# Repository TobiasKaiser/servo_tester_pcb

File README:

TO-263 footprint from https://github.com/cpavlina/kicad-pcblib

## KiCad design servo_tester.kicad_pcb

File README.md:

servo_tester
============
*An electronics project for me to learn how to design PCBs in KiCad and assemble it with SMD components.*

Purpose
-------

* Generate a PWM signal of approximately 20 ms period with variable duty cycle.
* The duty cycle can be controlled by a potentiometer.
* For user feedback, the currently set value should be displayed on a 4 digit seven-segment display.
* Through an additional push button, the user should be able to cycle through a number of settings to control parameters of the PWM output.
* This PWM output can be used to control the position of a servo motor.
* To have more, interesting stuff on the board, I put a little buck converter (instead of a linear voltage regulator like the 7805) on the board.

Hardware
--------

**Corrected** circuit here:
...

**Note: Some of the hardware problems which are corrected in this circuit file are not yet corrected in the board file.**

Hardware Problems
-----------------

As I expected, not everything worked out with the first PCBs and components that I have ordered. 

* Before the manufactured PCBs arrived, I already noticed that R5, R6, R7, R8 are incorrectly placed at the common electrode of the multiplexed seven-segment LED display.
Using the regular way of multiplexing this display, this would have resulted in different brightnesses depending on the number of lights turned on of each digit.
I could 

* The resistor R1 was incorrectly connecting the feedback output of the step down converter with VCC instead of GND.
I could solve this problem by adding the resistor right between beside two adjacent pins of the switching converter.

* Some of the capacitors that I have ordered were too large and could not fit on the PCB, and the push button switch that I ordered was accidentally a through-hole part. 
Next time I should spend a little more time on selecting the matching components. 

* Ground plane connection issue. 

* ADC problem (see next section)

Reading the potentiometer without built-in ADC module
-----------------------------------------------------

Unfortunately, the ATtiny2313 has no built-in ADC. The conversion has to be done somehow else using a comparator therefore.
The first attempt was to use the technique described in the Atmel application note AVR401 (the charging transient of the capacitor at the analog comparator input A is used to determine the current value of the analog comparator input B, which is the potentiometer).
This turned out to be too inaccurate.

Firmware
--------

The firmware can be found in the separate repository (servo_tester_firmware)[https://github.com/TobiasKaiser/servo_tester_firmware].

License
-------

* TO-263 footprint from https://github.com/cpavlina/kicad-pcblib
* Different license for Poti.pretty (see Poti.pretty/LICENSE.md)

For everything else:

Copyright (c) 2016 Tobias Kaiser <mail@tb-kaiser.de>

Permission is hereby granted, free of charge, to any person obtaining a copy of this hardware, software, and associated documentation files (the "Product"), to deal in the Product without restriction, including without limitation the rights to use, copy, modify, merge, publish, distribute, sublicense, and/or sell copies of the Product, and to permit persons to whom the Product is furnished to do so, subject to the following conditions:

The above copyright notice and this permission notice shall be included in all copies or substantial portions of the Product.

THE PRODUCT IS PROVIDED "AS IS", WITHOUT WARRANTY OF ANY KIND, EXPRESS OR IMPLIED, INCLUDING BUT NOT LIMITED TO THE WARRANTIES OF MERCHANTABILITY, FITNESS FOR A PARTICULAR PURPOSE AND NONINFRINGEMENT. IN NO EVENT SHALL THE AUTHORS OR COPYRIGHT HOLDERS BE LIABLE FOR ANY CLAIM, DAMAGES OR OTHER LIABILITY, WHETHER IN AN ACTION OF CONTRACT, TORT OR OTHERWISE, ARISING FROM, OUT OF OR IN CONNECTION WITH THE PRODUCT OR THE USE OR OTHER DEALINGS IN THE PRODUCT.

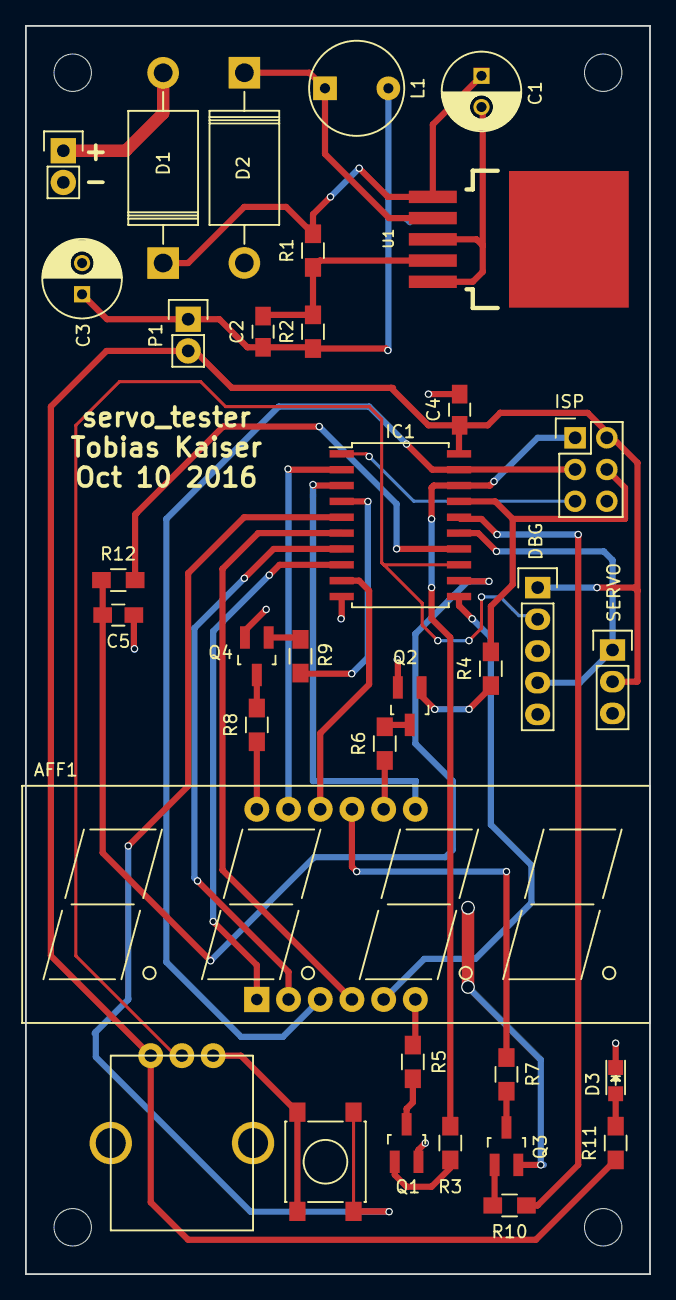
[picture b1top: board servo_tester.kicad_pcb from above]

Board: 2 copper layers, 50.0 x 100.0 mm, 35 parts (0 on the bottom side), 38 nets.

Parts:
AFF1: CC56-12; Cx56-12
C1: 470uF/50V; C_Radial_D6.3_L11.2_P2.5
C2: 10nF; C_0805_HandSoldering
C3: 470uF/10V; C_Radial_D6.3_L11.2_P2.5
C4: 100nF; C_0805_HandSoldering
C5: 4.7nF; C_0805_HandSoldering
D1, D2: 1N5825; Diode_DO-201AD_Horizontal_RM15
D3: LED; LED_0805
DBG: CONN_01X05; Pin_Header_Straight_1x05
IC1: ATTINY2313-S; SOIC-20_7.5x12.8mm_Pitch1.27mm
ISP: AVR-ISP-6; Pin_Header_Straight_2x03
L1: 68uH; INDUCTOR_V
P1, P2: CONN_01X02; Pin_Header_Straight_1x02
Q1, Q2, Q3, Q4: BC847; SOT-23_Handsoldering
R1, R3, R4, R9, R10, R11: 1k; R_0805_HandSoldering
R2: 3k; R_0805_HandSoldering
R5, R6, R7, R8: 300; R_0805_HandSoldering
R12: 27k; R_0805_HandSoldering
RV1: POT; POTI_PTV09A
SERVO: CONN_01X03; Pin_Header_Straight_1x03
SW1: SW_PUSH; SW_SPST_PTS645
U1: LM2596; TO-263-5

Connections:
+5V: C4.1, DBG.1, IC1.20, ISP.2, P1.2, R11.1, RV1.3, SERVO.2
+12V: D1.2, P2.1
/RST: IC1.1, ISP.5
/a: AFF1.11, IC1.2
/b: AFF1.7, IC1.3
/c: AFF1.4, IC1.6
/c1: IC1.4, R9.1
/c2: IC1.16, R10.1
/c3: IC1.17, ISP.4, R4.2
/c4: IC1.18, ISP.1, R3.2
/d: AFF1.2, IC1.7
/dp: AFF1.3, IC1.19, ISP.3
/e: AFF1.1, IC1.8
/f: AFF1.10, IC1.9
/g: AFF1.5, IC1.11
/pot_in: DBG.2, IC1.13, RV1.2
/pwm_out: DBG.4, IC1.15, SERVO.1
GND: C1.2, C3.2, C4.2, C5.1, D2.2, D3.1, DBG.5, IC1.10, ISP.6, P2.2, Q1.2, Q2.2, Q3.2, Q4.2, RV1.1, SERVO.3, SW1.2, U1.3, U1.5
unnamed: AFF1.6, R5.1
unnamed: AFF1.8, R6.1
unnamed: AFF1.9, R7.1
unnamed: AFF1.12, R8.1
unnamed: C1.1, D1.1, R1.2, U1.1
unnamed: C2.1, C3.1, L1.2, P1.1, R2.1
unnamed: C2.2, R1.1, R2.2, U1.4
unnamed: C5.2, IC1.12, R12.1
unnamed: D2.1, L1.1, U1.2
unnamed: D3.2, R11.2
unnamed: IC1.5, SW1.1
unnamed: IC1.14, R12.2
unnamed: Q1.1, R3.1
unnamed: Q1.3, R5.2
unnamed: Q2.1, R4.1
unnamed: Q2.3, R6.2
unnamed: Q3.1, R10.2
unnamed: Q3.3, R7.2
unnamed: Q4.1, R9.2
unnamed: Q4.3, R8.2

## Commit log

2016-10-09 added some stuff
2016-10-10 almost done.
    now still need to forward-annotate 1x 100nF decoupeling capacitor and maybe a LED.
2016-10-10 save before forward annotate test
2016-10-10 starting with drc now
2016-10-10 oops... attiny2313 doesnt have adc...
2016-10-10 adjusted - adc now via AVR400 application note
2016-10-10 final check again...
2016-10-10 Submitted to seeedstudio
2016-11-06 First firmware attempt: Using AVR 400
    ADC via step charging capacitor and comparing with pot.
    This works well when the servo PWM is unchanged, but does not work well if the servo pwm changes.
2016-11-06 Different A/D conversion algorithm implemented
2016-11-10 Added missing license file for pot footprint
2016-11-10 (Unfinished) readme added
2016-11-10 added user interface idea
2016-11-10 fixed 2 problems in schematic (3 -> 8 Rs, reglt.)
2016-11-12 ground connection fix, pcb still neds new netlist
2017-02-21 cleanup
